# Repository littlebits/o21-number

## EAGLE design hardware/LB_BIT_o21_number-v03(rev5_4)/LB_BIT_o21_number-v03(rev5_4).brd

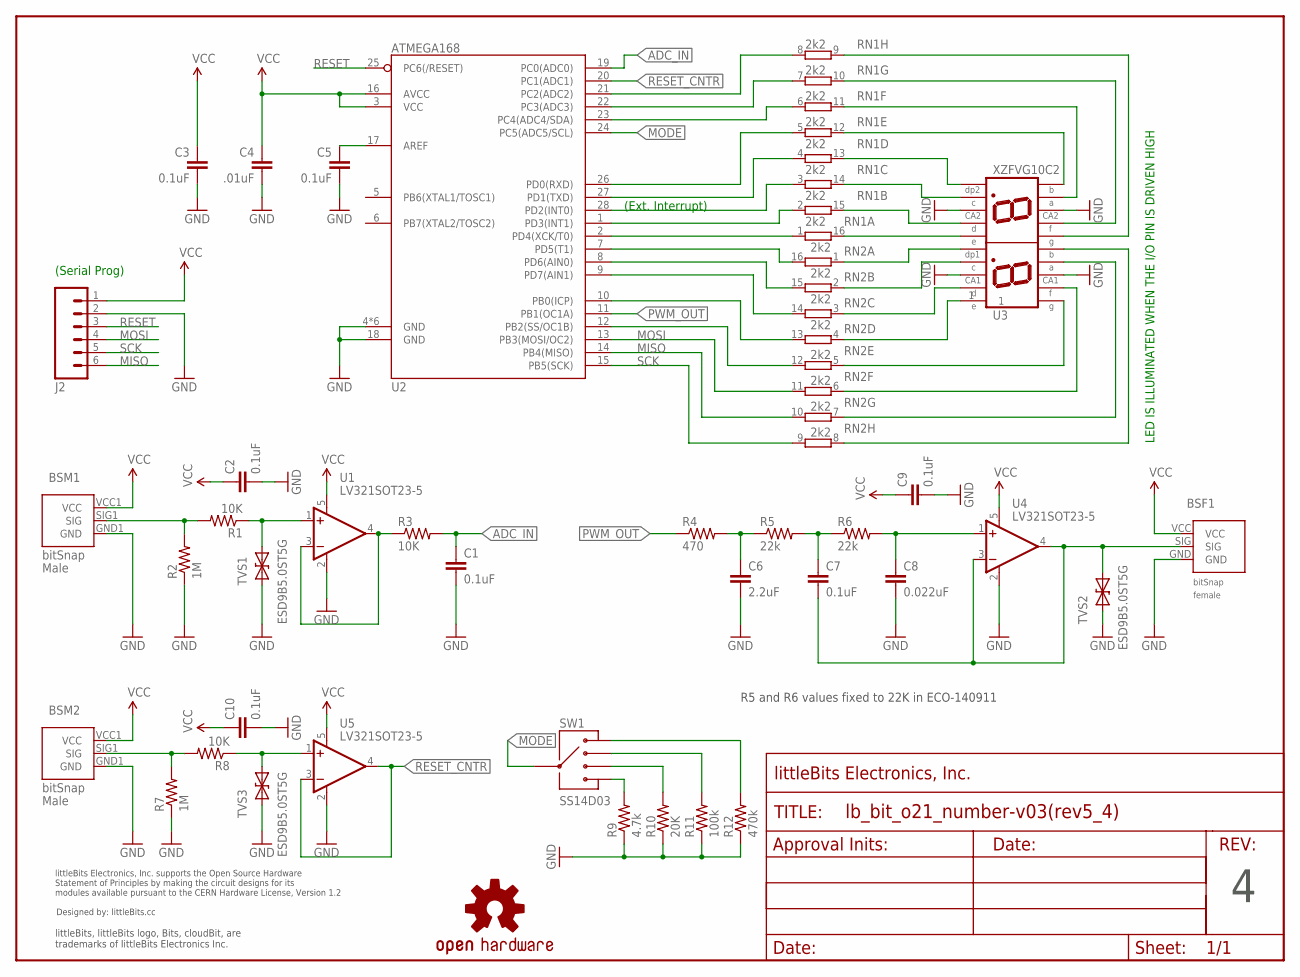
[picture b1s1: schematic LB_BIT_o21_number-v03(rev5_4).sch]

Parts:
BSF1: BITSNAP_V03_FEMALE
BSM1, BSM2: BITSNAP_V03_MALE
C1, C2, C3, C5, C7, C9, C10: 0.1uF; CAP-0603
C4: .01uF; CAP-0603
C6: 2.2uF; CAP-0603
C8: 0.022uF; CAP-0603
J2: HRD-60.1INCH_NO_SILKSCREEN; SIP6-SM-0.1IN-NOS.S.
R1, R3, R8: 10K; RES-0603
R2, R7: 1M; RES-0603
R4: 470; RES-0603
R5, R6: 22k; RES-0603
R9: 4.7k; RES-0603
R10: 20K; RES-0603
R11: 100k; RES-0603
R12: 470k; RES-0603
RN1, RN2: 2k2; EXB2HV
SW1: SS14D03; SWITCH-SLIDE-SP4T-SS14D03
TVS1, TVS2, TVS3: ESD9B5.0ST5G; SOD-923
U1, U4, U5: LV321SOT23-5; SOT23-5
U2: ATMEGA168; VQFN28
U3: XZFVG10C2; LED-DUAL7SEG-SM
U$1: FRAME-LETTER-OHWOHW; FABDWG01-OHW
U$2: OSHWCREDIT
U$27: OSHW-LOGOL; OSHW-LOGO-L

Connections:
ADC_IN: C1.1, R3.2, U2.19 (PC0(ADC0))
BIT_SIG: R3.1, U1.3 (-IN), U1.4 (OUT)
GND: BSF1.GND, BSM1.GND1 (GND), BSM2.GND1 (GND), C1.2, C2.2, C3.2, C4.2, C5.2, C6.2, C8.2, C9.2, C10.2, J2.2, R2.1, R7.1, R9.1, R10.1, R11.1, R12.1, TVS1.1 (A), TVS2.1 (A), TVS3.1 (A), U1.2 (V-), U2.4 (GND), U2.18 (GND), U2.TH (GND), U2.TH@1 (GND), U2.TH@2 (GND), U2.TH@3 (GND), U2.TH@4 (GND), U3.3, U3.8, U3.13, U3.18, U4.2 (V-), U5.2 (V-)
MISO: J2.6, RN2.10 (2), U2.14 (PB4(MISO))
MODE: SW1.COM, U2.24 (PC5(ADC5/SCL))
MOSI: J2.4, RN2.11 (2), U2.13 (PB3(MOSI/OC2))
unnamed: RN1.7 (1), U2.22 (PC3(ADC3))
unnamed: RN1.8 (1), U2.21 (PC2(ADC2))
unnamed: RN1.6 (1), U2.23 (PC4(ADC4/SDA))
unnamed: RN1.1, U2.2 (PD4(XCK/T0))
unnamed: RN1.2 (1), U2.1 (PD3(INT1))
unnamed: RN1.3 (1), U2.28 (PD2(INT0))
unnamed: RN1.4 (1), U2.27 (PD1(TXD))
unnamed: RN1.5 (1), U2.26 (PD0(RXD))
unnamed: RN2.16 (2), U2.7 (PD5(T1))
unnamed: RN2.15 (2), U2.8 (PD6(AIN0))
unnamed: RN2.14 (2), U2.9 (PD7(AIN1))
unnamed: RN2.13 (2), U2.10 (PB0(ICP))
unnamed: RN2.12 (2), U2.12 (PB2(SS/OC1B))
unnamed: C6.1, R4.2, R5.1
unnamed: C7.1, R5.2, R6.1
unnamed: RN1.16 (2), U3.6
unnamed: RN1.12 (2), U3.11
unnamed: RN1.11 (2), U3.12
unnamed: RN1.10 (2), U3.14
unnamed: RN1.9 (2), U3.15
unnamed: RN1.13 (2), U3.10
unnamed: RN1.15 (2), U3.7
unnamed: RN1.14 (2), U3.9
unnamed: C8.1, R6.2, U4.1 (+IN)
unnamed: RN2.1, U3.5
unnamed: RN2.2 (1), U3.4
unnamed: RN2.3 (1), U3.2
unnamed: RN2.4 (1), U3.1
unnamed: RN2.5 (1), U3.20
unnamed: RN2.6 (1), U3.19
unnamed: RN2.7 (1), U3.17
unnamed: RN2.8 (1), U3.16
unnamed: C5.1, U2.17 (AREF)
unnamed: R1.1, TVS1.2 (C), U1.1 (+IN)
unnamed: BSF1.SIG, C7.2, TVS2.2 (C), U4.3 (-IN), U4.4 (OUT)
unnamed: BSM2.SIG1 (SIG), R7.2, R8.2
unnamed: R12.2, SW1.1
unnamed: R8.1, TVS3.2 (C), U5.1 (+IN)
unnamed: R11.2, SW1.2
unnamed: R10.2, SW1.3
unnamed: R9.2, SW1.4
PWM_OUT: R4.1, U2.11 (PB1(OC1A))
RESET: J2.3, U2.25 (PC6(/RESET))
RESET_CNTR: U2.20 (PC1(ADC1)), U5.3 (-IN), U5.4 (OUT)
SCK: J2.5, RN2.9 (2), U2.15 (PB5(SCK))
SIG: BSM1.SIG1 (SIG), R1.2, R2.2
VCC: BSF1.VCC, BSM1.VCC1 (VCC), BSM2.VCC1 (VCC), C2.1, C3.1, C4.1, C9.1, C10.1, J2.1, U1.5 (V+), U2.3 (VCC), U2.16 (AVCC), U4.5 (V+), U5.5 (V+)

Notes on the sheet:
(Ext. Interrupt)
(Serial Prog)
LED IS ILLUMINATED WHEN THE I/O PIN IS DRIVEN HIGH
R5 and R6 values fixed to 22K in ECO-140911

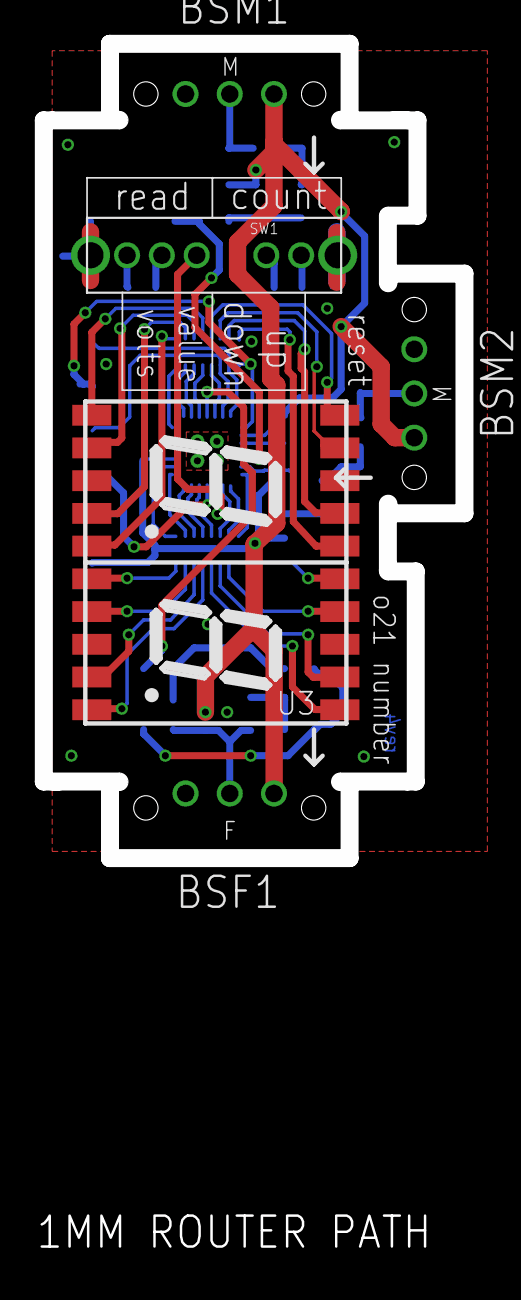
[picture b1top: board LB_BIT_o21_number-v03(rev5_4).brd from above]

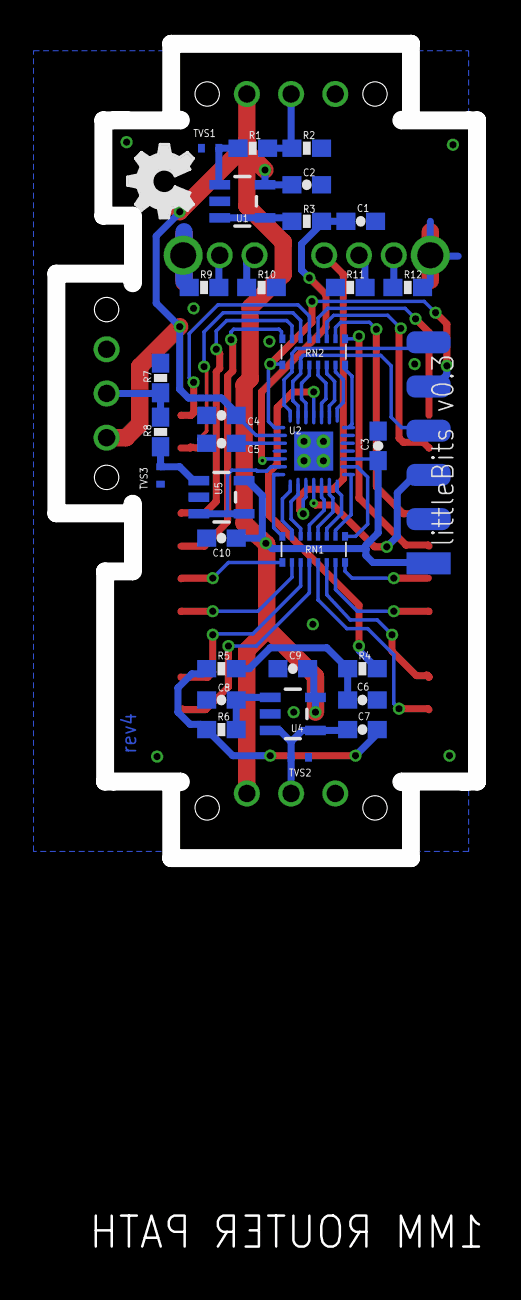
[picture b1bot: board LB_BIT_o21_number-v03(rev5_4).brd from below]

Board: 2 copper layers, 24.9 x 69.7 mm, 42 parts (32 on the bottom side), 53 nets.

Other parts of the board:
DRILEGEND: DRILEGEND
U$20: OSHW_FILLX150_NOTEXT

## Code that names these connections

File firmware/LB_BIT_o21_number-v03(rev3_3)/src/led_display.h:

/*
 * led_display.h\
 *
 * Created: 5/22/2014 5:18:23 PM
 *
 * Copyright 2014 littleBits Electronics
 *
 * This file is part of o21-number.
 *
 * o21-number is free software: you can redistribute it and/or modify
 * it under the terms of the GNU General Public License as published by
 * the Free Software Foundation, either version 3 of the License, or
 * (at your option) any later version.
 *
 * o21-number is distributed in the hope that it will be useful,
 * but WITHOUT ANY WARRANTY; without even the implied warranty of
 * MERCHANTABILITY or FITNESS FOR A PARTICULAR PURPOSE.  See the
 * GNU General Public License at <http://www.gnu.org/licenses/> for more details.
 *
 * This file incorporates work covered by the following copyright and
 * permission notice:
 *
 *	Copyright 2013
 *	source: http://www.dsprelated.com/showcode/304.php
 *	
 *	The code is released under Creative Commons Attribution 3.0. See the license
 * 	at <https://creativecommons.org/licenses/by/3.0/us/legalcode> for more details.
 */ 


#ifndef LED_DISPLAY_H_
#define LED_DISPLAY_H_

#define LEFT_A (1 << PB4)
#define LEFT_B (1 << PB5)
#define LEFT_C (1 << PD6)
#define LEFT_D (1 << PD7)
#define LEFT_E (1 << PB0)
#define LEFT_F (1 << PB3)
#define LEFT_G (1 << PB2)

#define RIGHT_A (1 << PC4)
#define RIGHT_B (1 << PD0)
#define RIGHT_C (1 << PD2)
#define RIGHT_D (1 << PD3)
#define RIGHT_E (1 << PD4)
#define RIGHT_F (1 << PC3)
#define RIGHT_G (1 << PC2)

#define DECIMAL_PT_L (1 << PD5)
#define DECIMAL_PT_R (1 << PD1)


// This enumeration will be used in the display_decimal() function below:
enum decimal_point {OFF, ON};

// This function will control the pin that drives the decimal point of the LED display
inline void display_decimal(int decimal_status)
{
	if(decimal_status == ON)
	PORTD |= DECIMAL_PT_L;			// Turn the LED display for decimal point on
	else 						// else assume decimal_status == OFF, so:
	PORTD &= ~DECIMAL_PT_L;			// Turn the LED display for decimal point off
}

// This function specifies the behavior of the pins that drive the LED display.
// Setting a '1' in these ports designates the pins as outputs (as opposed to inputs or something else)

inline void init_led_outputs()
{
	DDRB |= LEFT_A|LEFT_B|LEFT_E|LEFT_F|LEFT_G;
	DDRC |= RIGHT_A|RIGHT_F|RIGHT_G;
	DDRD |= LEFT_C|LEFT_D|RIGHT_B|RIGHT_C|RIGHT_D|RIGHT_E|DECIMAL_PT_L|DECIMAL_PT_R;
}

///////////////////////////////////////////////////////////////////////////////////////////////////////////////////////////
///////////////////// The following functions control the pins that drive the LED display's left digit ////////////////////
///////////////////////////////////////////////////////////////////////////////////////////////////////////////////////////


void l_zero()
{
	PORTB |= LEFT_A|LEFT_B|LEFT_E|LEFT_F;
	PORTB &= ~LEFT_G;
	
	PORTD |= LEFT_C|LEFT_D;
}

void l_one()
{
	PORTB |= LEFT_B;
	PORTB &= ~(LEFT_A|LEFT_E|LEFT_F|LEFT_G);

	PORTD |= LEFT_C;
	PORTD &= ~LEFT_D;
}

void l_two()
{
	PORTB |= LEFT_A|LEFT_B|LEFT_E|LEFT_G;
	PORTB &= ~LEFT_F;

	PORTD |= LEFT_D;
	PORTD &= ~LEFT_C;
}

void l_three()
{
	PORTB |= LEFT_A|LEFT_B|LEFT_G;
	PORTB &= ~(LEFT_F|LEFT_E);

	PORTD |= LEFT_C|LEFT_D;
}

void l_four()
{
	PORTB |= LEFT_F|LEFT_B|LEFT_G;
	PORTB &= ~(LEFT_A|LEFT_E);

	PORTD |= LEFT_C;
	PORTD &= ~LEFT_D;
}

void l_five()
{
	PORTB |= LEFT_A|LEFT_F|LEFT_G;
	PORTB &= ~(LEFT_B|LEFT_E);

	PORTD |= LEFT_C|LEFT_D;
}

void l_six()
{
	PORTB |= LEFT_A|LEFT_E|LEFT_F|LEFT_G;
	PORTB &= ~LEFT_B;

	PORTD |= LEFT_C|LEFT_D;
}

void l_seven()
{
	PORTB |= LEFT_A|LEFT_B;
	PORTB &= ~(LEFT_E|LEFT_F|LEFT_G);

	PORTD |= LEFT_C;
	PORTD &= ~LEFT_D;
}

void l_eight()
{
	PORTB |= LEFT_A|LEFT_B|LEFT_E|LEFT_F|LEFT_G;

	PORTD |= LEFT_C|LEFT_D;
}

void l_nine()
{
	PORTB |= LEFT_A|LEFT_B|LEFT_E|LEFT_F|LEFT_G;
	PORTB &= ~LEFT_E;

	PORTD |= LEFT_C|LEFT_D;
}




////////////////////////////////////////////////////////////////////////////////////////////////////////////////////////////
///////////////////// The following functions control the pins that drive the LED display's right digit ////////////////////
////////////////////////////////////////////////////////////////////////////////////////////////////////////////////////////

void r_zero()
{
	PORTC |= RIGHT_A|RIGHT_F;
	PORTC &= ~RIGHT_G;

	PORTD |= RIGHT_B|RIGHT_C|RIGHT_D|RIGHT_E;
}

void r_one()
{
	PORTC &= ~(RIGHT_A|RIGHT_F|RIGHT_G);

	PORTD |= RIGHT_B|RIGHT_C;
	PORTD &= ~(RIGHT_D|RIGHT_E);
}

void r_two()
{
	PORTC |= RIGHT_A|RIGHT_G;
	PORTC &= ~RIGHT_F;

	PORTD |= RIGHT_B|RIGHT_D|RIGHT_E;
	PORTD &= ~RIGHT_C;
}

void r_three()
{
	PORTC |= RIGHT_A|RIGHT_G;
	PORTC &= ~RIGHT_F;

	PORTD |= RIGHT_B|RIGHT_D|RIGHT_C;
	PORTD &= ~RIGHT_E;
}

void r_four()
{
	PORTC |= RIGHT_G|RIGHT_F;
	PORTC &= ~RIGHT_A;

	PORTD |= RIGHT_B|RIGHT_C;
	PORTD &= ~(RIGHT_E|RIGHT_D);
}

void r_five()
{
	PORTC |= RIGHT_A|RIGHT_F|RIGHT_G;

	PORTD |= RIGHT_D|RIGHT_C;
	PORTD &= ~(RIGHT_B|RIGHT_E);
}

void r_six()
{
	PORTC |= RIGHT_A|RIGHT_F|RIGHT_G;

	PORTD |= RIGHT_C|RIGHT_D|RIGHT_E;
	PORTD &= ~RIGHT_B;
}

void r_seven()
{
	PORTC &= ~(RIGHT_F|RIGHT_G);
	PORTC |= RIGHT_A;

	PORTD |= RIGHT_C|RIGHT_B;
	PORTD &= ~(RIGHT_D|RIGHT_E);
}

void r_eight()
{
	PORTC |= RIGHT_A|RIGHT_F|RIGHT_G;

	PORTD |= RIGHT_B|RIGHT_C|RIGHT_D|RIGHT_E;
}

void r_nine()
{
	PORTC |= RIGHT_A|RIGHT_F|RIGHT_G;

	PORTD |= RIGHT_B|RIGHT_C|RIGHT_D;
	PORTD &= ~RIGHT_E;
}


///////////////////////////////////////////////////////////////////////////////////////////////////////////////////////////
///	These are arrays of pointers to functions. These arrays function like lookup tables for the left and			///
/// 	right display numbers. The functions that we point to control the GPIO pins that drive the LED displays		///
///////////////////////////////////////////////////////////////////////////////////////////////////////////////////////////

void (*display_left[10])(void) = {l_zero, l_one, l_two, l_three, l_four, l_five, l_six, l_seven, l_eight, l_nine};
void (*display_right[10])(void) = {r_zero, r_one, r_two, r_three, r_four, r_five, r_six, r_seven, r_eight, r_nine};





#endif /* LED_DISPLAY_H_ */

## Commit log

2014-11-11 First commit, added hardware and software files
2014-11-13 Added readme
2014-11-13 Altered credits
2014-11-18 Added firmware and hardware for new rev 5_4
2015-02-21 Replaces src for 3_3 with correct version

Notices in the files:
parts and their libraries:
LITTLEBITS: modules available pursuant to the CERN Hardware License,
Version 1.2
SparkFun: Licensing: CC v3.0 Share-Alike You are welcome to use this library for commercial purposes.
LITTLEBITS: modules available pursuant to the CERN Hardware License, Version 1.2
